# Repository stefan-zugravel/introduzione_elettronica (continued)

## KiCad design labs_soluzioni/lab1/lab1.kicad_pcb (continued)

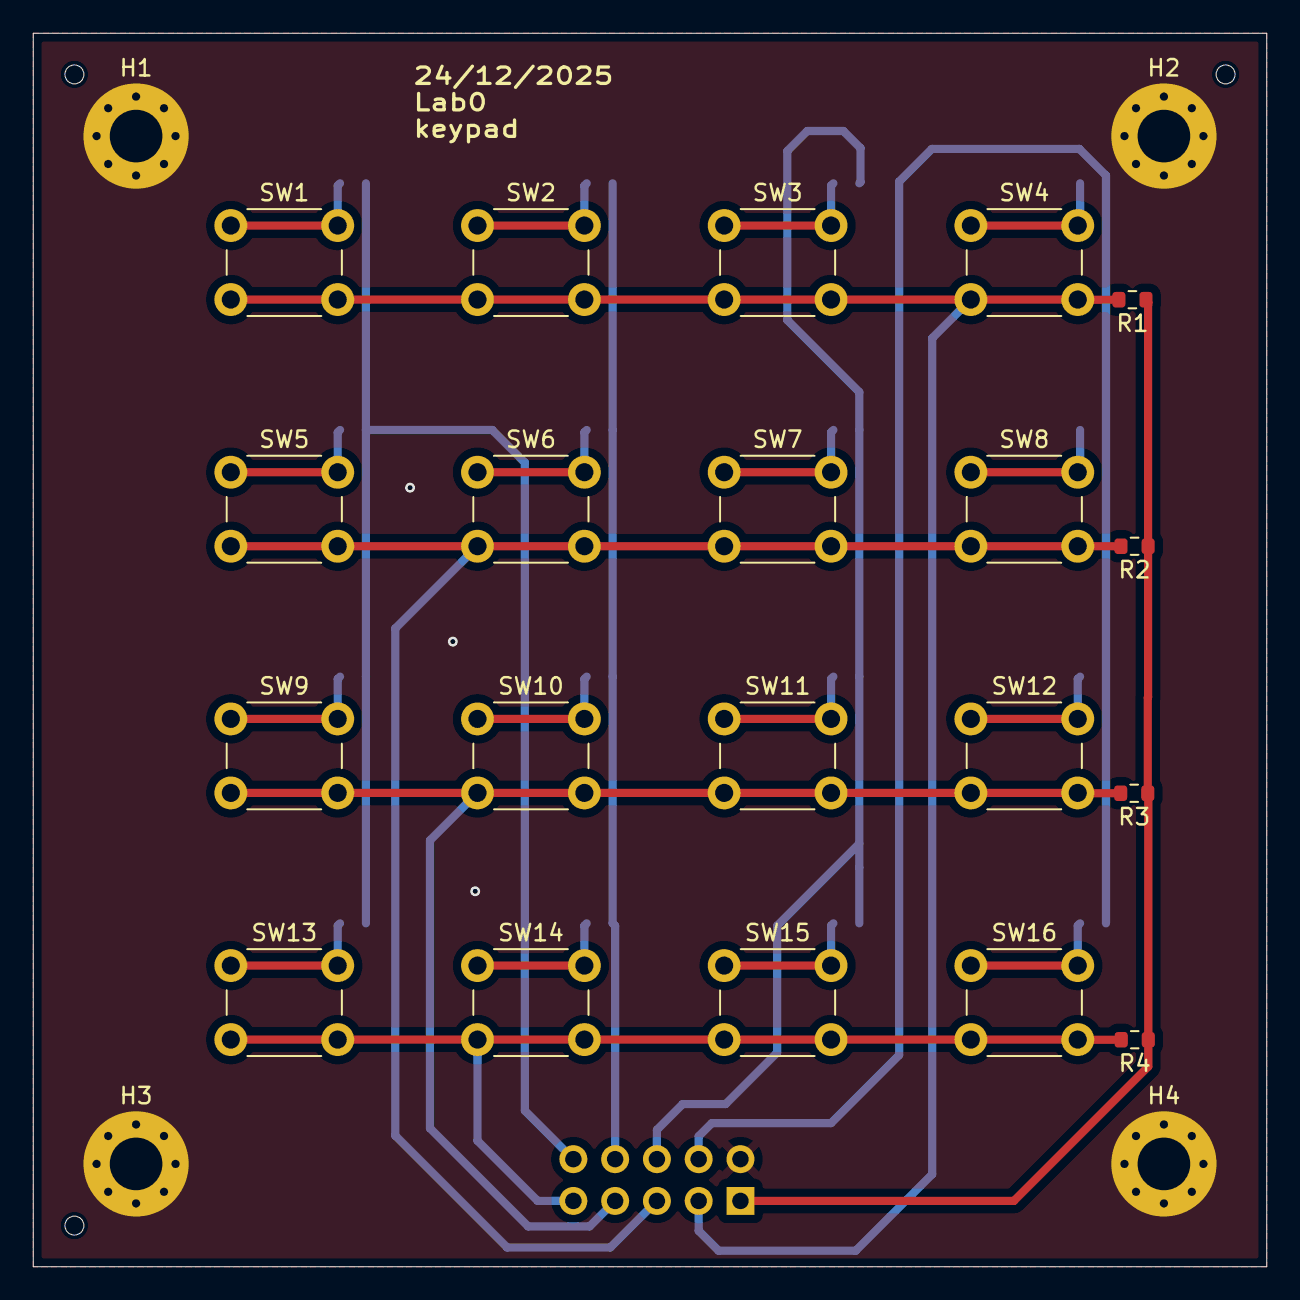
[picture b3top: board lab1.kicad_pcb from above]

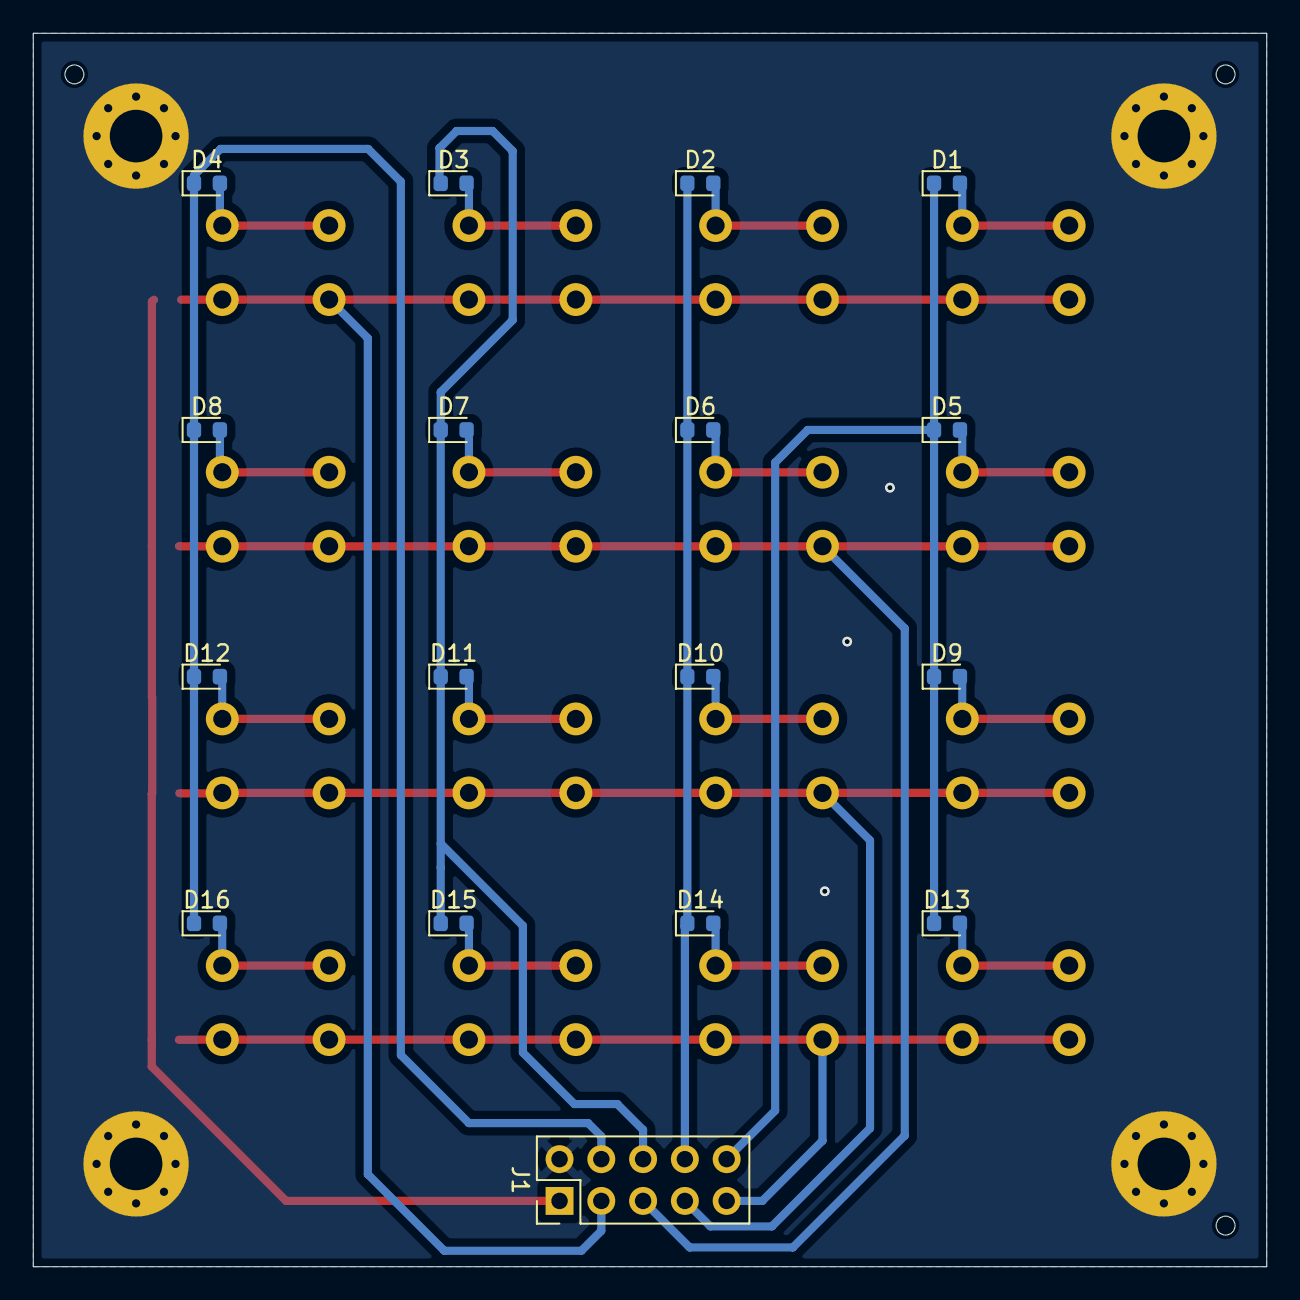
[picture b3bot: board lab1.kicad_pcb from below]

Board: 2 copper layers, 75.0 x 75.0 mm, 44 parts (17 on the bottom side), 26 nets.

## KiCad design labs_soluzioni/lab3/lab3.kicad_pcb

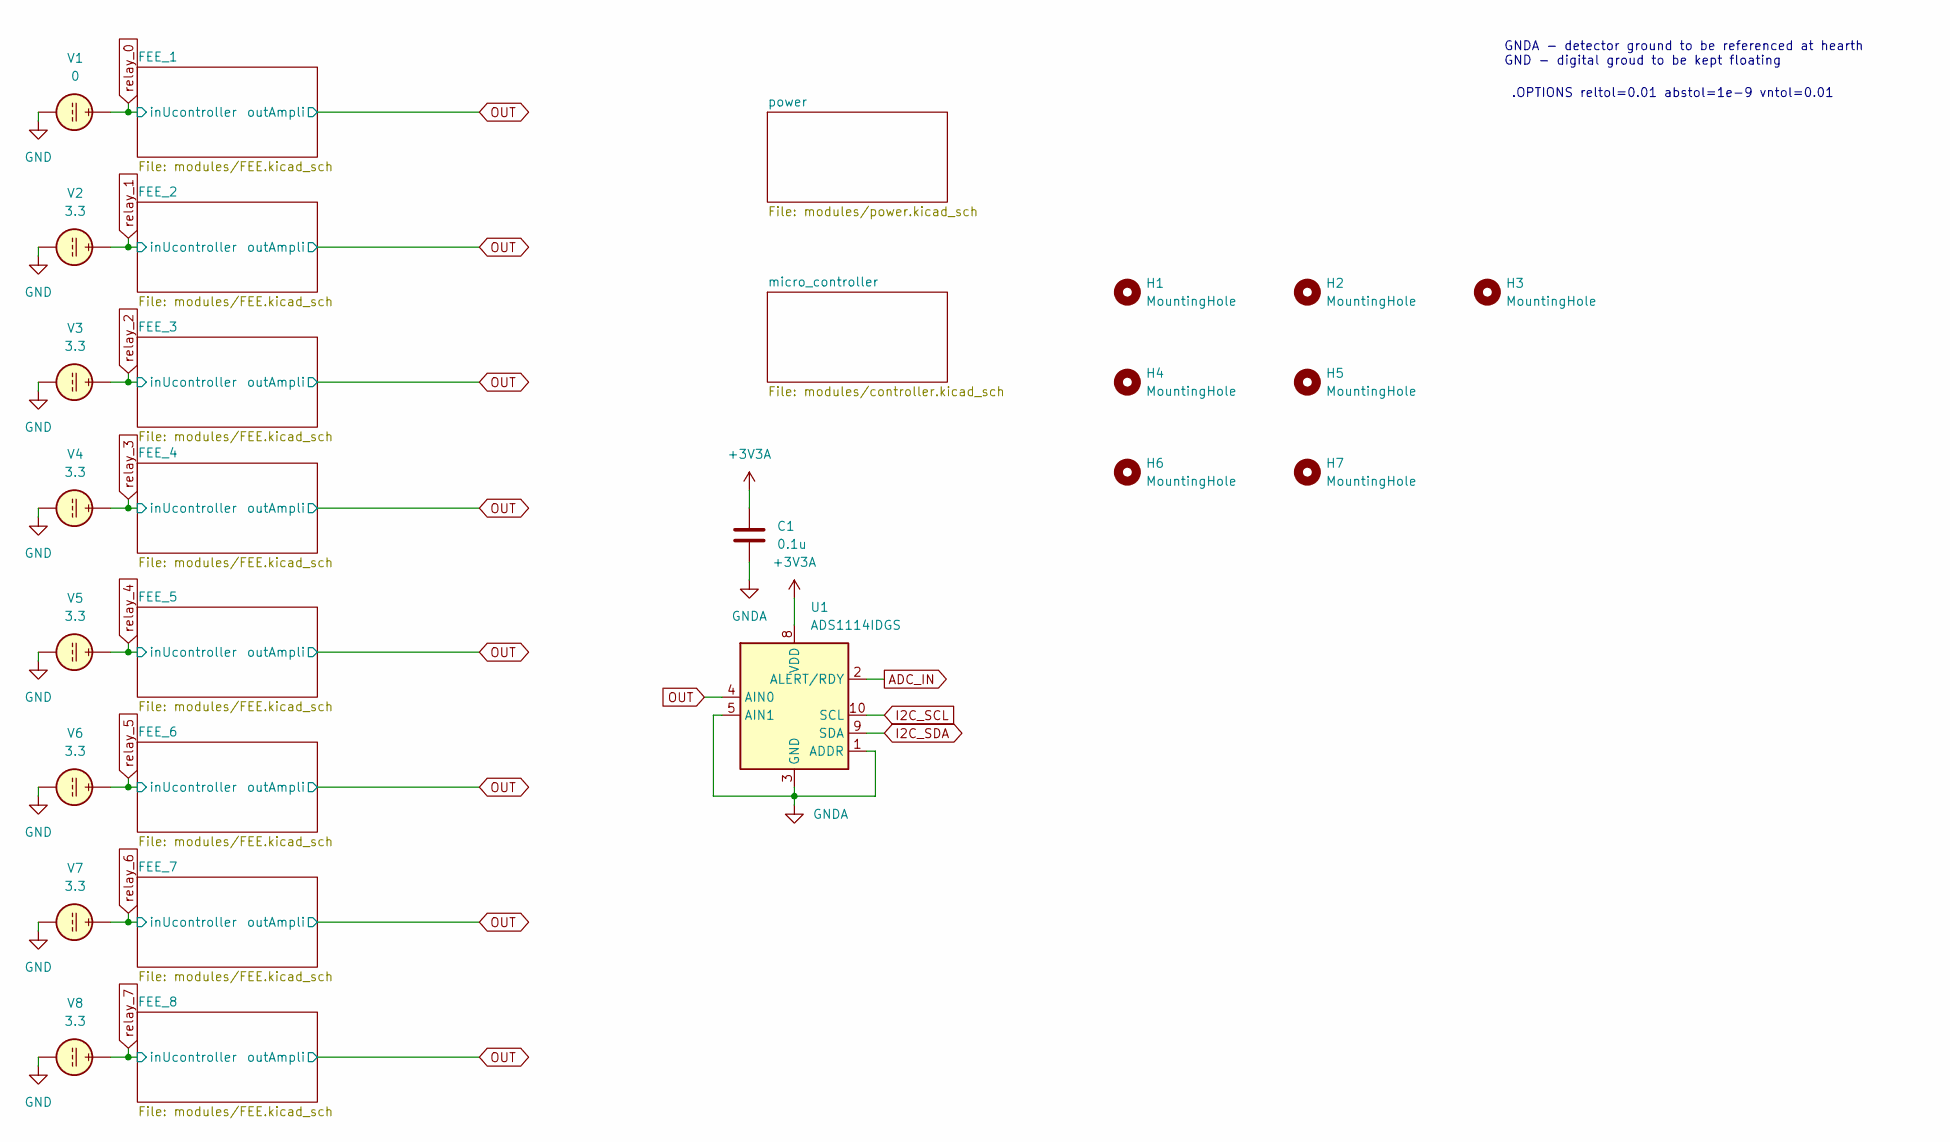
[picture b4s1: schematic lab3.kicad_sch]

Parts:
C1: 0.1u; C_0603_1608Metric
H1, H2, H3: MountingHole; ToolingHole_1.152mm
H4, H5, H6, H7: MountingHole; MountingHole_3.2mm_M3_DIN965
U1: ADS1114IDGS; TSSOP-10_3x3mm_P0.5mm
V1: 0
V2, V3, V4, V5, V6, V7, V8: 3.3

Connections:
+3V3A: C1.1, U1.8 (VDD); also elsewhere on the board
ADC_IN: U1.2 (ALERT/RDY); also elsewhere on the board
GNDA: C1.2, U1.1 (ADDR), U1.3 (GND), U1.5 (AIN1); also elsewhere on the board
I2C_SCL: U1.10 (SCL); also elsewhere on the board
I2C_SDA: U1.9 (SDA); also elsewhere on the board
unnamed: V1.2, V2.2, V3.2, V4.2, V5.2, V6.2, V7.2, V8.2
OUT: U1.4 (AIN0); also elsewhere on the board

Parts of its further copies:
C9: 0.1u; C_0603_1608Metric

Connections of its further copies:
+3V3A: C9.1; also elsewhere on the board
GNDA: C9.2; also elsewhere on the board

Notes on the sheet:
.OPTIONS reltol=0.01 abstol=1e-9 vntol=0.01
GNDA - detector ground to be referenced at hearth GND - digital groud to be kept floating

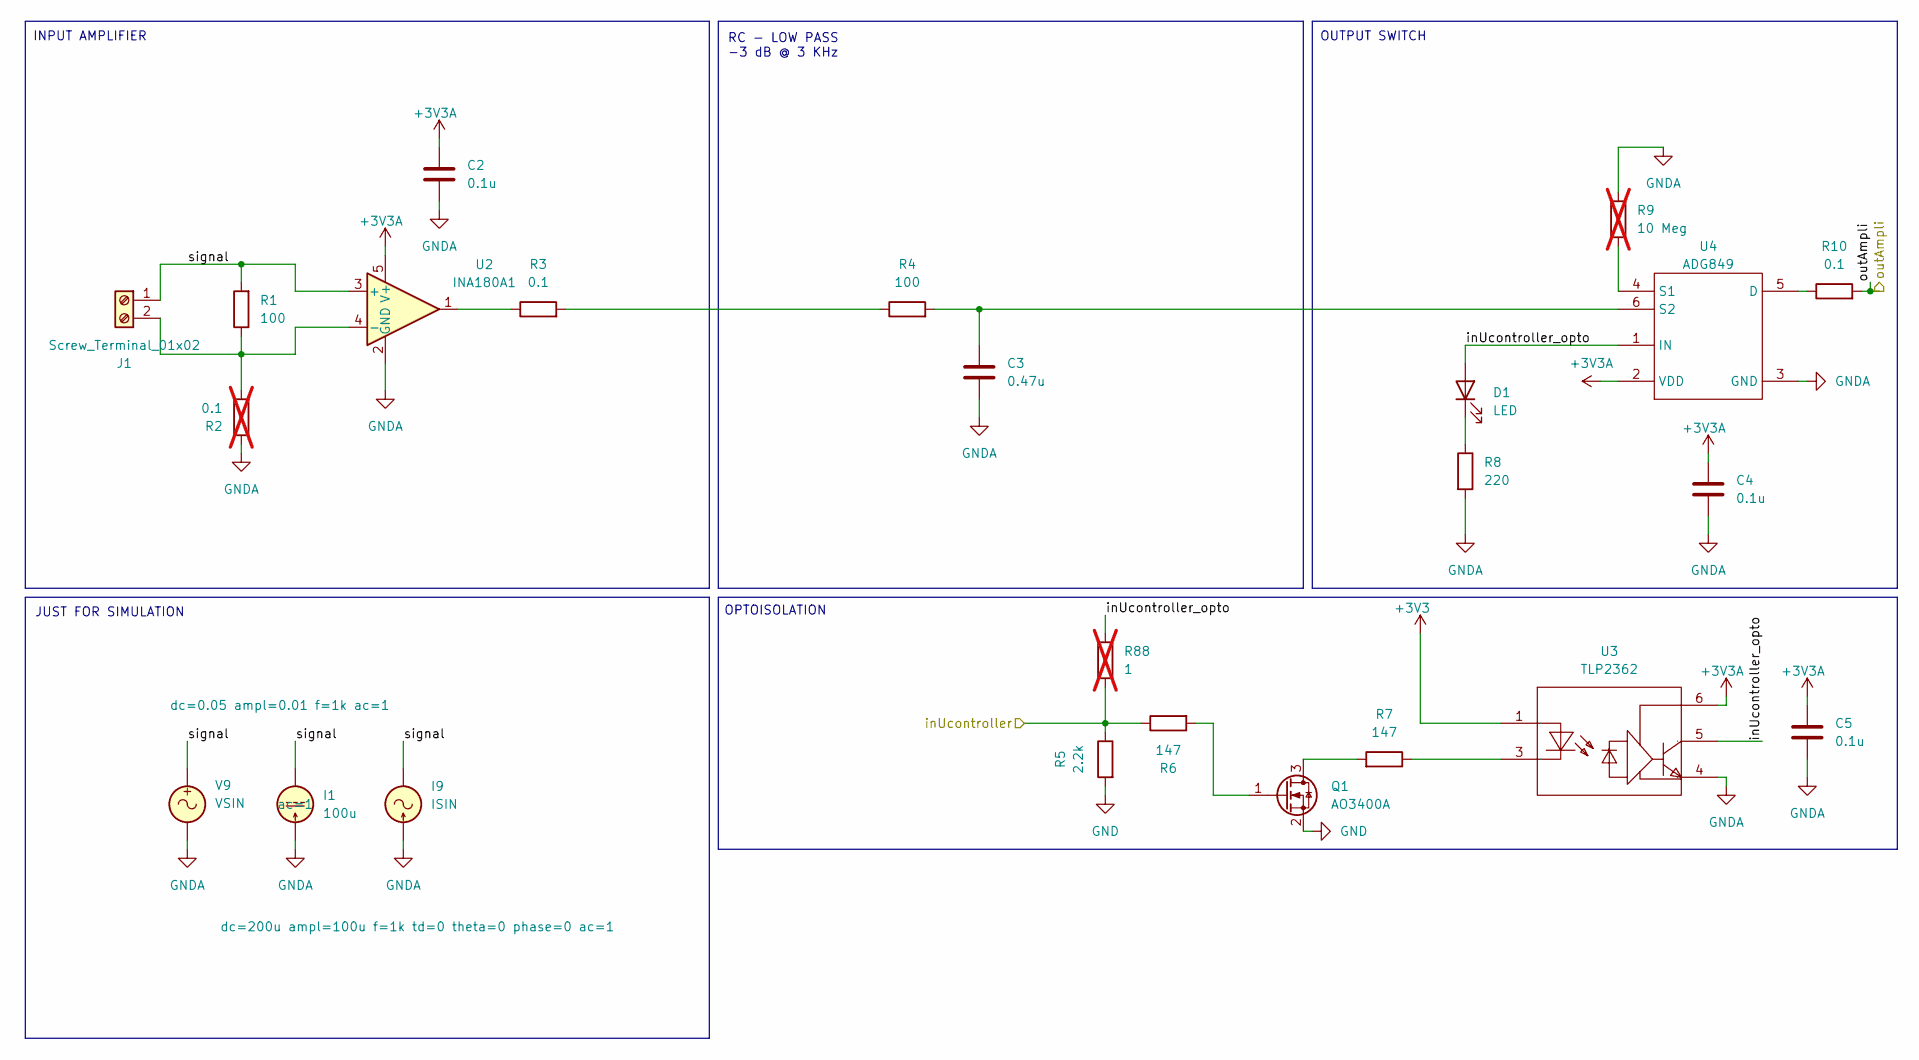
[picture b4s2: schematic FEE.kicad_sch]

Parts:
C2, C4, C5: 0.1u; C_0603_1608Metric
C3: 0.47u; C_0603_1608Metric
D1: LED; LED_0603_1608Metric
I1: 100u
I9: ISIN
J1: Screw_Terminal_01x02; PhoenixContact_GMSTBA_2,5_2-G-7,62_1x02_P7.62mm_Horizontal
Q1: AO3400A; SOT-23; jlc C20917
R1, R4: 100; R_0603_1608Metric
R2: 0.1; R_0603_1608Metric; not fitted
R3, R10: 0.1; R_0603_1608Metric
R5: 2.2k; R_0603_1608Metric
R6, R7: 147; R_0603_1608Metric
R8: 220; R_0603_1608Metric
R9: 10 Meg; R_0603_1608Metric; not fitted
R88: 1; R_0603_1608Metric; not fitted
U2: INA180A1; SOT-23-5
U3: TLP2362; OPTO-SMD-5_L3.7-W4.6-P1.27-LS7.0-BR; Manufacturer Part TLP2362(TPL,E; LCSC Part Name DC输入 1通道 隔离电压(rms):3750V
U4: ADG849; SOT-363_SC-70-6; Manufacturer Part ADG849YKSZ-REEL7; LCSC Part Name 3 V/5 V CMOS 0.5Ω SPDT/2:1多路复用器在SC70封装中
V9: VSIN

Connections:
+3V3: U3.1; also elsewhere on the board
+3V3A: C2.2, C4.1, C5.1, U2.5 (V+), U3.6, U4.2 (VDD); also elsewhere on the board
/FEE_1/inUcontroller_opto: D1.2 (A), U3.5, U4.1 (IN)
/FEE_1/signal: J1.1, R1.2, U2.3 (+)
GND: Q1.2 (S), R5.2; also elsewhere on the board
GNDA: C2.1, C3.2, C4.2, C5.2, I1.1, I9.1, R2.1, R8.2, R9.1, U2.2 (GND), U3.4, U4.3 (GND), V9.2; also elsewhere on the board
unnamed: D1.1 (K), R8.1
unnamed: J1.2, R1.1, R2.2, U2.4 (-)
unnamed: Q1.3 (D), R7.2
unnamed: Q1.1 (G), R6.2
unnamed: R3.1, U2.1
unnamed: R3.2, R4.1
unnamed: R7.1, U3.3
unnamed: R10.1, U4.5 (D)
unnamed: R9.2, U4.4 (S1)
unnamed: C3.1, R4.2, U4.6 (S2)
OUT: R10.2; also elsewhere on the board
relay_0: R5.1, R6.1; also elsewhere on the board

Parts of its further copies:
C6, C8, C9, C10, C12, C13, C14, C16, C17, C18, C20, C21, C22, C24, C25, C26, C28, C29, C30, C32, C33: 0.1u; C_0603_1608Metric
C7, C11, C15, C19, C23, C27, C31: 0.47u; C_0603_1608Metric
D3, D5, D7, D9, D11, D13, D15: LED; LED_0603_1608Metric
J2, J3, J4, J5, J6, J7, J8: Screw_Terminal_01x02; PhoenixContact_GMSTBA_2,5_2-G-7,62_1x02_P7.62mm_Horizontal
Q2, Q3, Q4, Q5, Q6, Q7, Q8: AO3400A; SOT-23; jlc C20917
R11, R14, R21, R24, R31, R34, R41, R44, R51, R54, R61, R64, R71, R74: 100; R_0603_1608Metric
R12, R22, R32, R42, R52, R62, R72: 0.1; R_0603_1608Metric; not fitted
R13, R20, R23, R30, R33, R40, R43, R50, R53, R60, R63, R70, R73, R80: 0.1; R_0603_1608Metric
R15, R25, R35, R45, R55, R65, R75: 2.2k; R_0603_1608Metric
R16, R17, R26, R27, R36, R37, R46, R47, R56, R57, R66, R67, R76, R77: 147; R_0603_1608Metric
R18, R28, R38, R48, R58, R68, R78: 220; R_0603_1608Metric
R19, R29, R39, R49, R59, R69, R79: 10 Meg; R_0603_1608Metric; not fitted
U5, U8, U11, U14, U17, U20, U23: INA180A1; SOT-23-5
U6, U9, U12, U15, U18, U21, U24: TLP2362; OPTO-SMD-5_L3.7-W4.6-P1.27-LS7.0-BR; Manufacturer Part TLP2362(TPL,E; LCSC Part Name DC输入 1通道 隔离电压(rms):3750V
U7, U10, U13, U16, U19, U22, U25: ADG849; SOT-363_SC-70-6; Manufacturer Part ADG849YKSZ-REEL7; LCSC Part Name 3 V/5 V CMOS 0.5Ω SPDT/2:1多路复用器在SC70封装中

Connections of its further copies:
+3V3: U6.1, U9.1, U12.1, U15.1, U18.1, U21.1, U24.1; also elsewhere on the board
+3V3A: C6.2, C8.1, C9.1, C10.2, C12.1, C13.1, C14.2, C16.1, C17.1, C18.2, C20.1, C21.1, C22.2, C24.1, C25.1, C26.2, C28.1, C29.1, C30.2, C32.1, C33.1, U5.5 (V+), U6.6, U7.2 (VDD), U8.5 (V+), U9.6, U10.2 (VDD), U11.5 (V+), U12.6, U13.2 (VDD), U14.5 (V+), U15.6, U16.2 (VDD), U17.5 (V+), U18.6, U19.2 (VDD), U20.5 (V+), U21.6, U22.2 (VDD), U23.5 (V+), U24.6, U25.2 (VDD); also elsewhere on the board
/FEE_2/inUcontroller_opto: D3.2 (A), U6.5, U7.1 (IN)
/FEE_2/signal: J2.1, R11.2, U5.3 (+)
/FEE_3/inUcontroller_opto: D5.2 (A), U9.5, U10.1 (IN)
/FEE_3/signal: J3.1, R21.2, U8.3 (+)
/FEE_4/inUcontroller_opto: D7.2 (A), U12.5, U13.1 (IN)
/FEE_4/signal: J4.1, R31.2, U11.3 (+)
/FEE_5/inUcontroller_opto: D9.2 (A), U15.5, U16.1 (IN)
/FEE_5/signal: J5.1, R41.2, U14.3 (+)
/FEE_6/inUcontroller_opto: D11.2 (A), U18.5, U19.1 (IN)
/FEE_6/signal: J6.1, R51.2, U17.3 (+)
/FEE_7/inUcontroller_opto: D13.2 (A), U21.5, U22.1 (IN)
/FEE_7/signal: J7.1, R61.2, U20.3 (+)
/FEE_8/inUcontroller_opto: D15.2 (A), U24.5, U25.1 (IN)
/FEE_8/signal: J8.1, R71.2, U23.3 (+)
GND: Q2.2 (S), Q3.2 (S), Q4.2 (S), Q5.2 (S), Q6.2 (S), Q7.2 (S), Q8.2 (S), R15.2, R25.2, R35.2, R45.2, R55.2, R65.2, R75.2; also elsewhere on the board
GNDA: C6.1, C7.2, C8.2, C9.2, C10.1, C11.2, C12.2, C13.2, C14.1, C15.2, C16.2, C17.2, C18.1, C19.2, C20.2, C21.2, C22.1, C23.2, C24.2, C25.2, C26.1, C27.2, C28.2, C29.2, C30.1, C31.2, C32.2, C33.2, R12.1, R18.2, R19.1, R22.1, R28.2, R29.1, R32.1, R38.2, R39.1, R42.1, R48.2, R49.1, R52.1, R58.2, R59.1, R62.1, R68.2, R69.1, R72.1, R78.2, R79.1, U5.2 (GND), U6.4, U7.3 (GND), U8.2 (GND), U9.4, U10.3 (GND), U11.2 (GND), U12.4, U13.3 (GND), U14.2 (GND), U15.4, U16.3 (GND), U17.2 (GND), U18.4, U19.3 (GND), U20.2 (GND), U21.4, U22.3 (GND), U23.2 (GND), U24.4, U25.3 (GND); also elsewhere on the board
unnamed: D3.1 (K), R18.1
unnamed: D5.1 (K), R28.1
unnamed: D7.1 (K), R38.1
unnamed: D9.1 (K), R48.1
unnamed: D11.1 (K), R58.1
unnamed: D13.1 (K), R68.1
unnamed: D15.1 (K), R78.1
unnamed: J2.2, R11.1, R12.2, U5.4 (-)
unnamed: J3.2, R21.1, R22.2, U8.4 (-)
unnamed: J4.2, R31.1, R32.2, U11.4 (-)
unnamed: J5.2, R41.1, R42.2, U14.4 (-)
unnamed: J6.2, R51.1, R52.2, U17.4 (-)
unnamed: J7.2, R61.1, R62.2, U20.4 (-)
unnamed: J8.2, R71.1, R72.2, U23.4 (-)
unnamed: Q2.3 (D), R17.2
unnamed: Q2.1 (G), R16.2
unnamed: Q3.3 (D), R27.2
unnamed: Q3.1 (G), R26.2
unnamed: Q4.3 (D), R37.2
unnamed: Q4.1 (G), R36.2
unnamed: Q5.3 (D), R47.2
unnamed: Q5.1 (G), R46.2
unnamed: Q6.3 (D), R57.2
unnamed: Q6.1 (G), R56.2
unnamed: Q7.3 (D), R67.2
unnamed: Q7.1 (G), R66.2
unnamed: Q8.3 (D), R77.2
unnamed: Q8.1 (G), R76.2
unnamed: R13.1, U5.1
unnamed: R13.2, R14.1
unnamed: R17.1, U6.3
unnamed: R23.1, U8.1
unnamed: R23.2, R24.1
unnamed: R27.1, U9.3
unnamed: R33.1, U11.1
unnamed: R33.2, R34.1
unnamed: R37.1, U12.3
unnamed: R43.1, U14.1
unnamed: R43.2, R44.1
unnamed: R47.1, U15.3
unnamed: R53.1, U17.1
unnamed: R53.2, R54.1
unnamed: R57.1, U18.3
unnamed: R63.1, U20.1
unnamed: R63.2, R64.1
unnamed: R67.1, U21.3
unnamed: R73.1, U23.1
unnamed: R73.2, R74.1
unnamed: R77.1, U24.3
unnamed: R20.1, U7.5 (D)
unnamed: R19.2, U7.4 (S1)
unnamed: C7.1, R14.2, U7.6 (S2)
unnamed: R30.1, U10.5 (D)
unnamed: R29.2, U10.4 (S1)
unnamed: C11.1, R24.2, U10.6 (S2)
unnamed: R40.1, U13.5 (D)
unnamed: R39.2, U13.4 (S1)
unnamed: C15.1, R34.2, U13.6 (S2)
unnamed: R50.1, U16.5 (D)
unnamed: R49.2, U16.4 (S1)
unnamed: C19.1, R44.2, U16.6 (S2)
unnamed: R60.1, U19.5 (D)
unnamed: R59.2, U19.4 (S1)
unnamed: C23.1, R54.2, U19.6 (S2)
unnamed: R70.1, U22.5 (D)
unnamed: R69.2, U22.4 (S1)
unnamed: C27.1, R64.2, U22.6 (S2)
unnamed: R80.1, U25.5 (D)
unnamed: R79.2, U25.4 (S1)
unnamed: C31.1, R74.2, U25.6 (S2)
OUT: R20.2, R30.2, R40.2, R50.2, R60.2, R70.2, R80.2; also elsewhere on the board
relay_1: R15.1, R16.1; also elsewhere on the board
relay_2: R25.1, R26.1; also elsewhere on the board
relay_3: R35.1, R36.1; also elsewhere on the board
relay_4: R45.1, R46.1; also elsewhere on the board
relay_5: R55.1, R56.1; also elsewhere on the board
relay_6: R65.1, R66.1; also elsewhere on the board
relay_7: R75.1, R76.1; also elsewhere on the board

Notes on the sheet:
INPUT AMPLIFIER
OUTPUT SWITCH
JUST FOR SIMULATION
OPTOISOLATION
RC - LOW PASS -3 dB @ 3 KHz

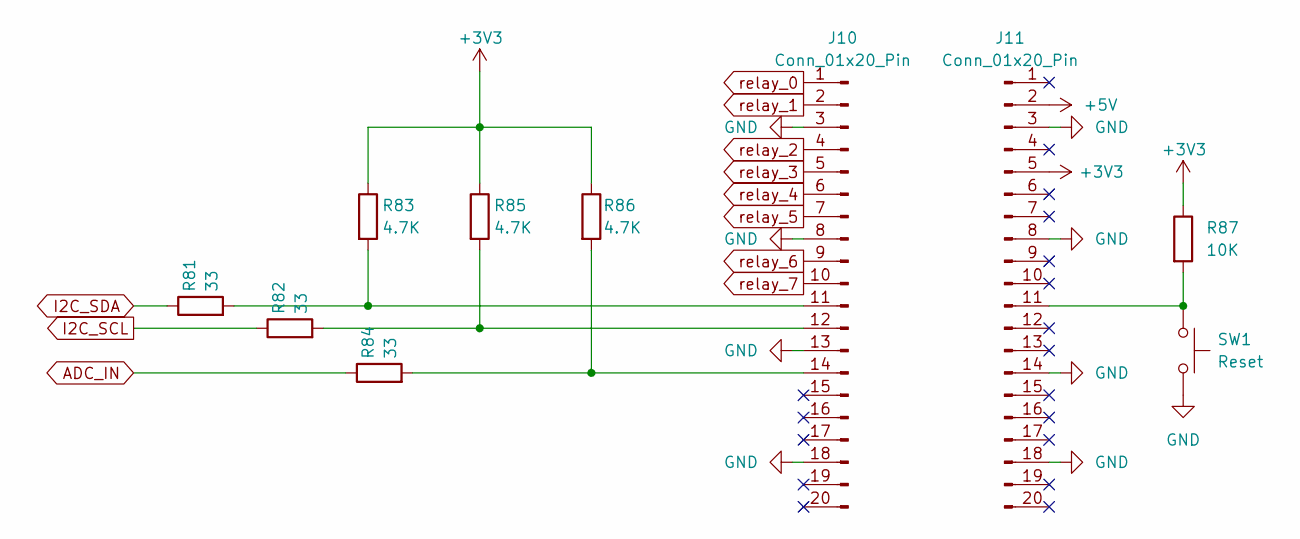
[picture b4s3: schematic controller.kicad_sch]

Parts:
J10, J11: Conn_01x20_Pin; PinHeader_1x20_P2.54mm_Vertical
R81, R82, R84: 33; R_0603_1608Metric
R83, R85, R86: 4.7K; R_0603_1608Metric
R87: 10K; R_0603_1608Metric
SW1: Reset; SW_PUSH_6mm

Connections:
+3V3: J11.5, R83.1, R85.1, R86.1, R87.1; also elsewhere on the board
+5V: J11.2; also elsewhere on the board
ADC_IN: R84.1; also elsewhere on the board
GND: J10.3, J10.8, J10.13, J10.18, J11.3, J11.8, J11.14, J11.18, SW1.2; also elsewhere on the board
I2C_SCL: R82.1; also elsewhere on the board
I2C_SDA: R81.1; also elsewhere on the board
unnamed: J10.11, R81.2, R83.2
unnamed: J10.12, R82.2, R85.2
unnamed: J10.14, R84.2, R86.2
unnamed: J11.11, R87.2, SW1.1
relay_0: J10.1; also elsewhere on the board
relay_1: J10.2; also elsewhere on the board
relay_2: J10.4; also elsewhere on the board
relay_3: J10.5; also elsewhere on the board
relay_4: J10.6; also elsewhere on the board
relay_5: J10.7; also elsewhere on the board
relay_6: J10.9; also elsewhere on the board
relay_7: J10.10; also elsewhere on the board

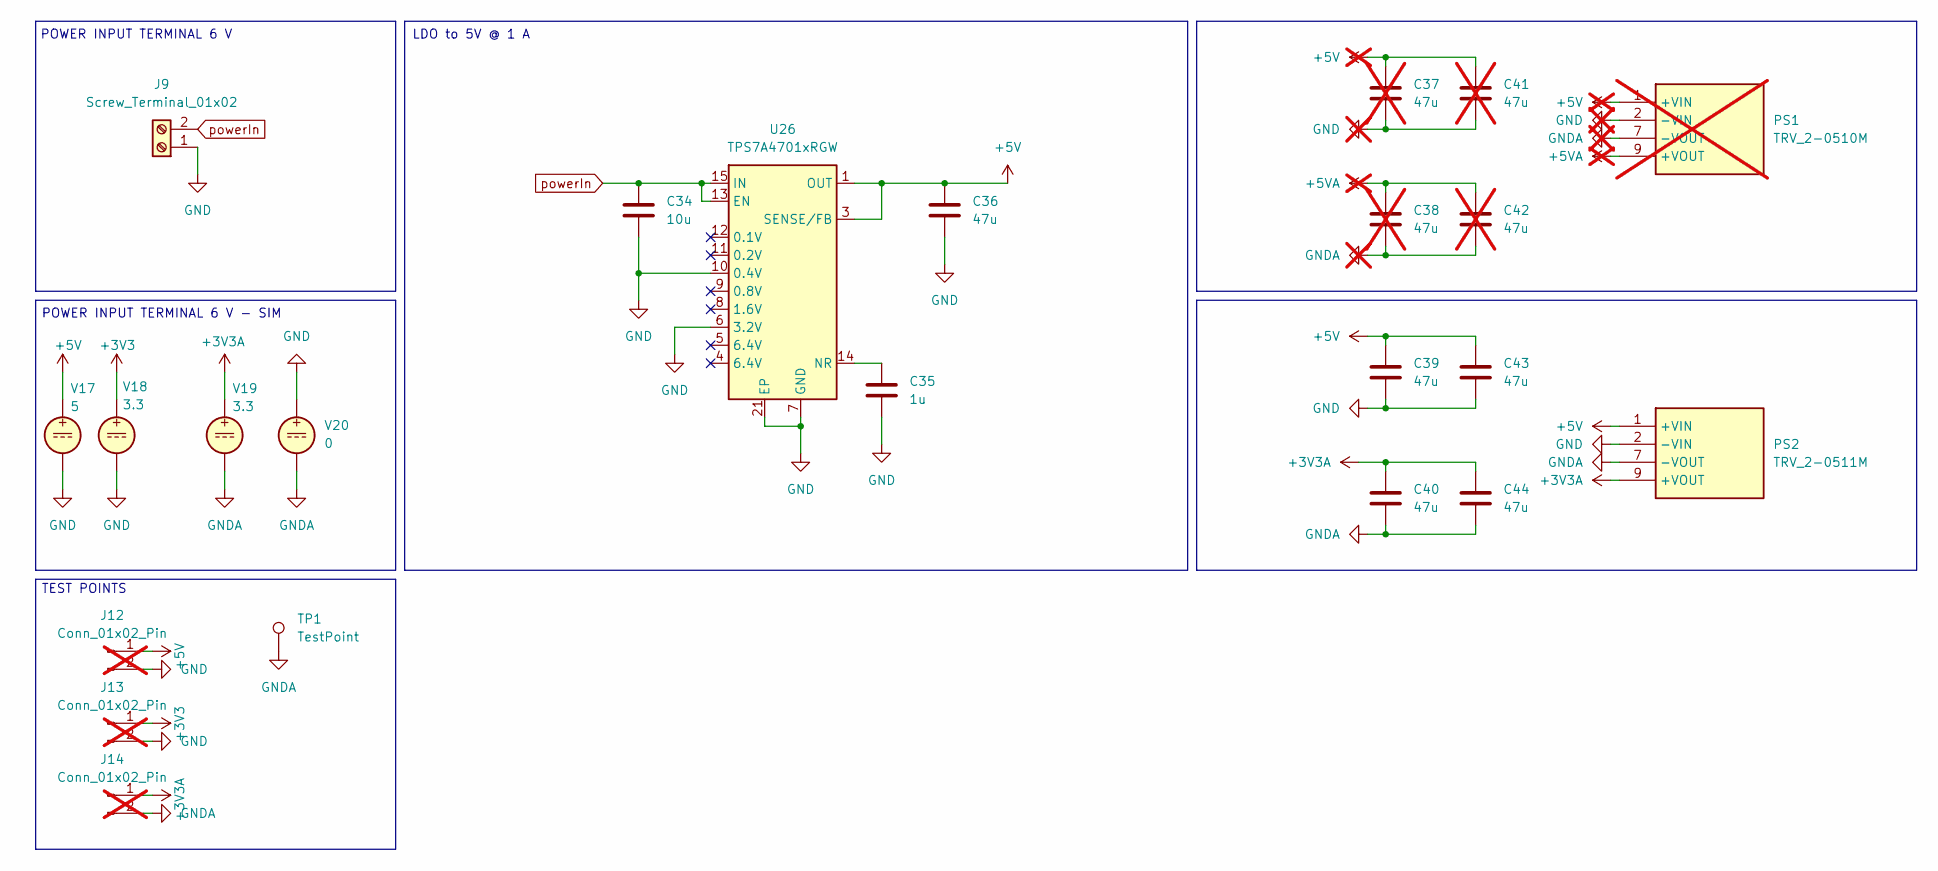
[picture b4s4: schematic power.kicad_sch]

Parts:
C34: 10u; C_0603_1608Metric
C35: 1u; C_0603_1608Metric
C36, C39, C40, C43, C44: 47u; C_0805_2012Metric
C37, C38, C41, C42: 47u; C_0805_2012Metric; not fitted
J9: Screw_Terminal_01x02; PhoenixContact_GMSTBA_2,5_2-G-7,62_1x02_P7.62mm_Horizontal
J12, J13, J14: Conn_01x02_Pin; PinHeader_1x02_P2.54mm_Vertical; not fitted
PS1: TRV_2-0510M; TRV20510M; Mouser Part Number 495-TRV2-0510M; not fitted
PS2: TRV_2-0511M; TRV20511M; Mouser Part Number 495-TRV2-0511M
TP1: TestPoint; TestPoint_Pad_D4.0mm
U26: TPS7A4701xRGW; Texas_RGW0020A_VQFN-20-1EP_5x5mm_P0.65mm_EP3.15x3.15mm_Ther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
V17: 5
V18, V19: 3.3
V20: 0

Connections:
+3V3: J13.1, V18.1; also elsewhere on the board
+3V3A: C40.1, C44.1, J14.1, PS2.9 (+VOUT), V19.1; also elsewhere on the board
+5V: C36.1, C39.1, C43.1, J12.1, PS2.1 (+VIN), U26.1 (OUT), U26.3 (SENSE/FB), U26.20 (OUT); also elsewhere on the board
GND: C34.2, C35.2, C36.2, C39.2, C43.2, J9.1, J12.2, J13.2, PS2.2 (-VIN), U26.6 (3.2V), U26.7 (GND), U26.10 (0.4V), U26.21 (EP); also elsewhere on the board
GNDA: C38.2, C40.2, C42.2, C44.2, J14.2, PS1.7 (-VOUT), PS2.7 (-VOUT), TP1.1, V19.2, V20.2; also elsewhere on the board
unnamed: C38.1, C42.1, PS1.9 (+VOUT)
unnamed: C35.1, U26.14 (NR)
powerIn: C34.1, J9.2, U26.13 (EN), U26.15 (IN), U26.16 (IN)

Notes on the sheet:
POWER INPUT TERMINAL 6 V
POWER INPUT TERMINAL 6 V - SIM
LDO to 5V @ 1 A
TEST POINTS

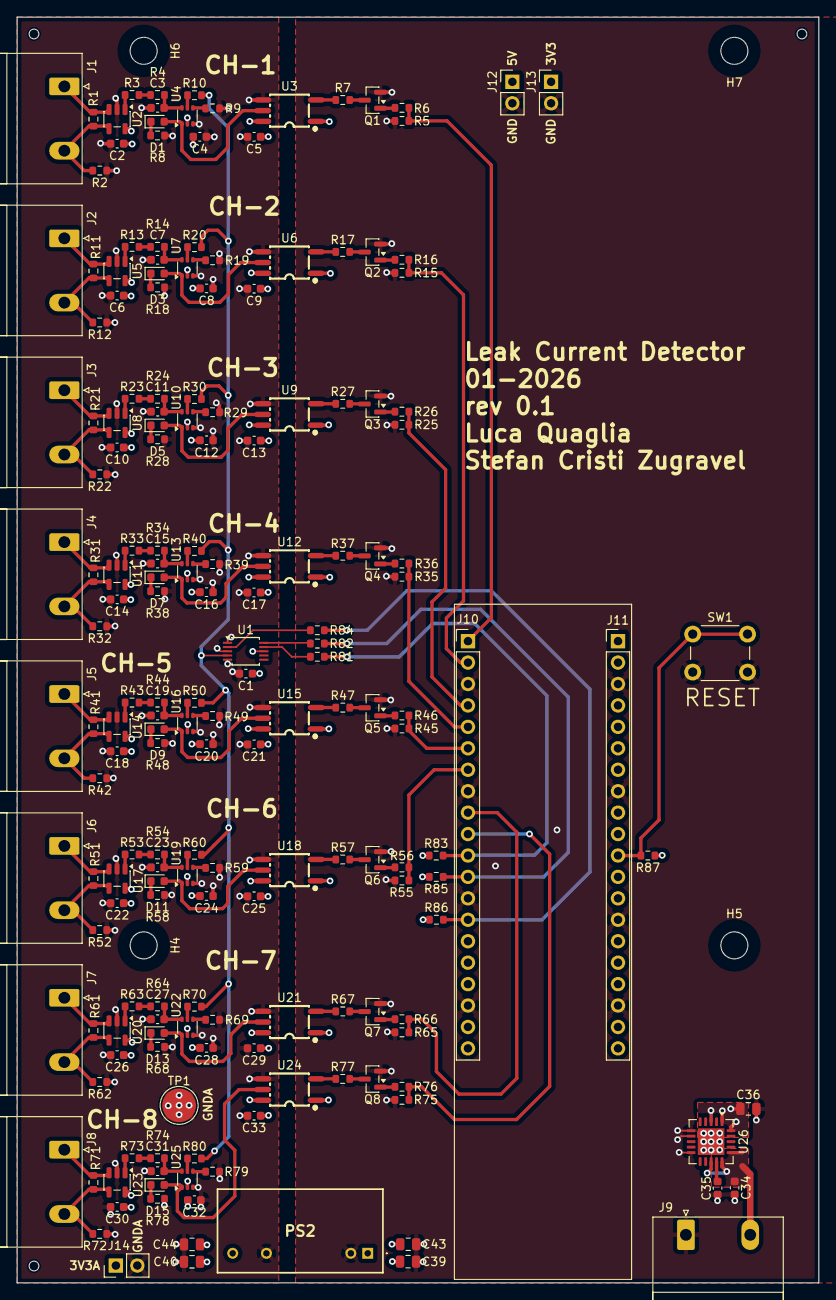
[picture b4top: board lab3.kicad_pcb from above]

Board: 6 copper layers, 95.0 x 150.0 mm, 193 parts (0 on the bottom side), 119 nets.

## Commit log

2026-02-10 Update .gitignore for VIVADO
2026-02-10 ADD labs KiCAD
2026-02-10 ADD work_area
2026-02-10 ADD lab6
2026-02-11 ADD lab7
2026-02-11 ADD lab8
2026-02-11 ADD lab9
2026-02-11 FIX lab9
2026-02-12 UPDATE lab1 and slides
2026-02-13 Source modification
2026-02-19 Update slides
2026-02-20 NEW lab4
